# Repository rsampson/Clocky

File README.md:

# Clocky

A simple desk clock for the ESP8266 / ESP32 with a web interface for configuration.

## Features

- Synchronizes time over NTP and automatically corrects for daylight saving time.
- Web interface for setting the time zone, alarm, and Wi-Fi credentials.
- Displays day of week, date, month, and 12-hour time.
- Hourly chime and settable alarm via a piezo beeper. The alarm plays "The Sailor's Hornpipe" on a loop until the touch pad is touched (a short alternative tune can be selected at compile time with `ALARM_TUNE` in [`src/Clocky.cpp`](src/Clocky.cpp)). Alarms have per-day scheduling (e.g. weekdays only) and a "next alarm" readout on the dashboard.
- Three display modes, stepped through with a touch pad: desk clock → stock indexes → sleep → desk clock.
- Stock-index mode that shows the current Dow, S&P 500, and Nasdaq Composite values (fetched from Yahoo Finance every 5 minutes while the mode is selected), each with an up/down marker versus the previous close. If the values can't be fetched (no Wi-Fi, no internet, the data source is down), this mode simply shows the normal clock until they can.
- Sleep mode that suppresses the display light and the hourly chime. The settable alarm still sounds in sleep mode (that's the point of an alarm) and is silenced with a touch.
- OTA (over-the-air) firmware updates via the web interface.

> [!CAUTION]
> This is a hobby project with no guarantees of reliability. Wi-Fi drops, NTP failures, power outages, and plain old bugs can all cause the alarm to not go off. Don't rely on it for anything you can't afford to be late for — the author is not responsible if it fails and you oversleep.

## Hardware Required

- ESP8266 (e.g. ESP12-F) or ESP32 (e.g. Wemos Lolin32)
- SSD1306 OLED display (128x32)
- Piezo beeper (optional — omit if no chime or alarm is needed)
- A touch pad made from any conductive material (required — see below)

### Wiring

| Component        | Pin |
|-------------------|-----|
| Piezo beeper       | D6 and D5 (piezo connected between them, not to GND) |
| Touch pad sensor   | D7  |
| Touch pad driver   | D3 (through a 300k resistor) |
| Status LED         | D4  |

The touch pad is the only input for switching the clock between desk clock, stock-index, and sleep modes, so it is not optional. It works by wiring the conductor directly to input pin D7, and also to output pin D3 through a 300k resistor. Touching the pad adds body capacitance to the circuit, which slows the signal from the driver pin to the sensor pin — this delay is what the firmware detects to register a touch.

The piezo is driven differentially on ESP8266: D5 always carries the inverse of D6, so connecting the piezo between D6 and D5 gives it twice the voltage swing (6.6 V peak to peak instead of 3.3 V), which makes it noticeably louder with no extra parts. A piezo wired from D6 to GND still works, just at the original volume. (ESP32 builds drive D6 only.)

Pin assignments and other hardware constants can be changed in [`src/config.h`](src/config.h).

## Building and Flashing

This is a [PlatformIO](https://platformio.org/) project (see [`platformio.ini`](platformio.ini) for the board configuration and library dependencies).

```bash
pio run                       # build
pio run -t upload             # build and flash over serial
pio device monitor            # serial monitor (115200 baud)
```

## Getting Started

1. Flash the firmware as above.
2. On first boot, the clock starts its own access point. Connect to it and open `192.168.4.1` in a browser.
3. Enter your Wi-Fi router's SSID and password to join the clock to your LAN.
4. Once connected, the clock is reachable at `clocky.local` (mDNS) or the IP assigned by your router.
5. Use the web interface to set the time zone, configure the alarm, and perform OTA firmware updates (no serial connection needed after this point).

### Web Dashboard

| Status | Alarm | Setup |
|---|---|---|
|  |  |  |

## Project Structure

```
platformio.ini    Board configuration and library dependencies
src/
  config.h         Hardware constants: pins, display size, tones, touch sensitivity
  Clocky.cpp        Entry point (setup/loop)
  wifi_manager.*     Wi-Fi connection state machine / AP fallback
  time_manager.*      NTP sync and time zone handling
  web_server.*          AsyncWebServer instance, routes, and JSON REST API
  web_assets.*            Embedded HTML/CSS/JS for the web dashboard
  debug.cpp                  Debug log telemetry
```

## Notes

- Confirm the board setting in [`src/config.h`](src/config.h) matches your actual hardware (ESP32 vs. ESP8266) — a mismatch will cause unpredictable behavior.
- The default hostname is `clocky`; this can be changed in [`src/config.h`](src/config.h).

## License

[MIT](src/LICENSE)

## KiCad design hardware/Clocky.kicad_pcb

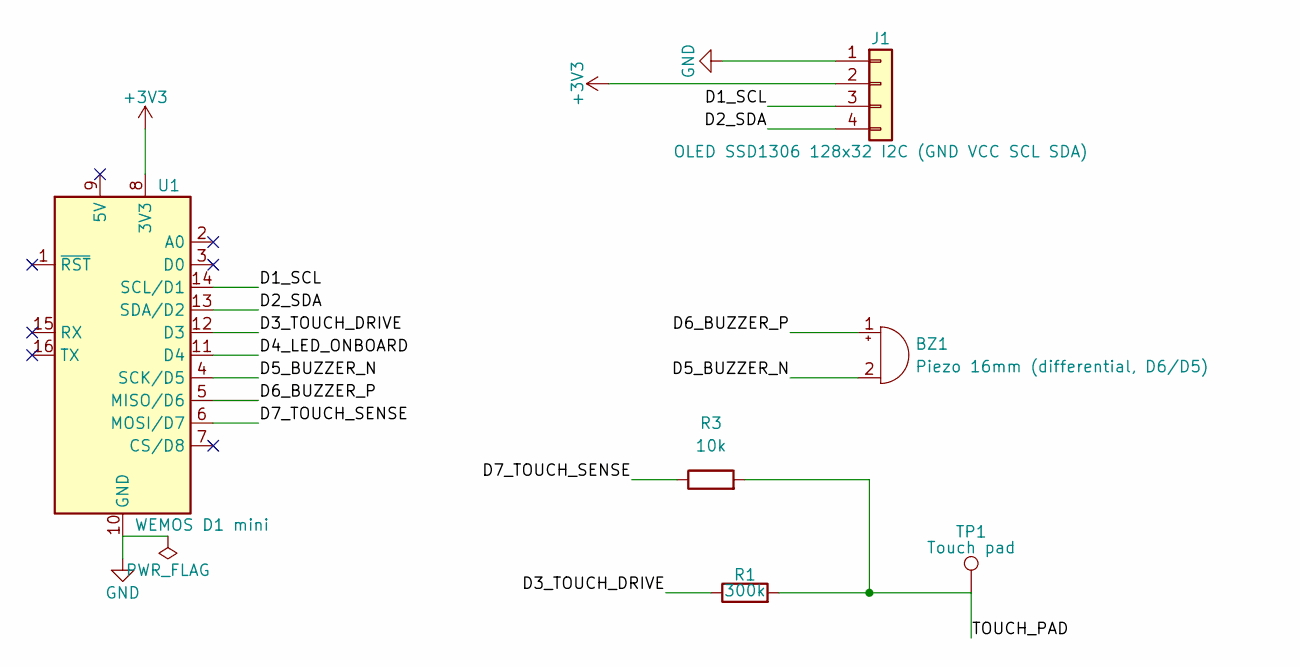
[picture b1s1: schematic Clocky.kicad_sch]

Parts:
BZ1: Piezo 16mm (differential, D6/D5); Buzzer_D16mm_P8mm
J1: OLED SSD1306 128x32 I2C (GND VCC SCL SDA); PinHeader_1x04_P2.54mm_Vertical
R1: 300k; R_Axial_DIN0207_L6.3mm_D2.5mm_P10.16mm_Horizontal
R3: 10k; R_Axial_DIN0207_L6.3mm_D2.5mm_P10.16mm_Horizontal
TP1: Touch pad; TestPoint_Pad_D4.0mm
U1: WEMOS D1 mini; WEMOS_D1_mini_light

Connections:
+3V3: J1.2, U1.8 (3V3)
/D1_SCL: J1.3, U1.14 (SCL/D1)
/D2_SDA: J1.4, U1.13 (SDA/D2)
/D3_TOUCH_DRIVE: R1.1, U1.12 (D3)
/D4_LED_ONBOARD: U1.11 (D4)
/D5_BUZZER_N: BZ1.2 (-), U1.4 (SCK/D5)
/D6_BUZZER_P: BZ1.1 (+), U1.5 (MISO/D6)
/D7_TOUCH_SENSE: R3.1, U1.6 (MOSI/D7)
/TOUCH_PAD: R1.2, R3.2, TP1.1
GND: J1.1, U1.10 (GND)

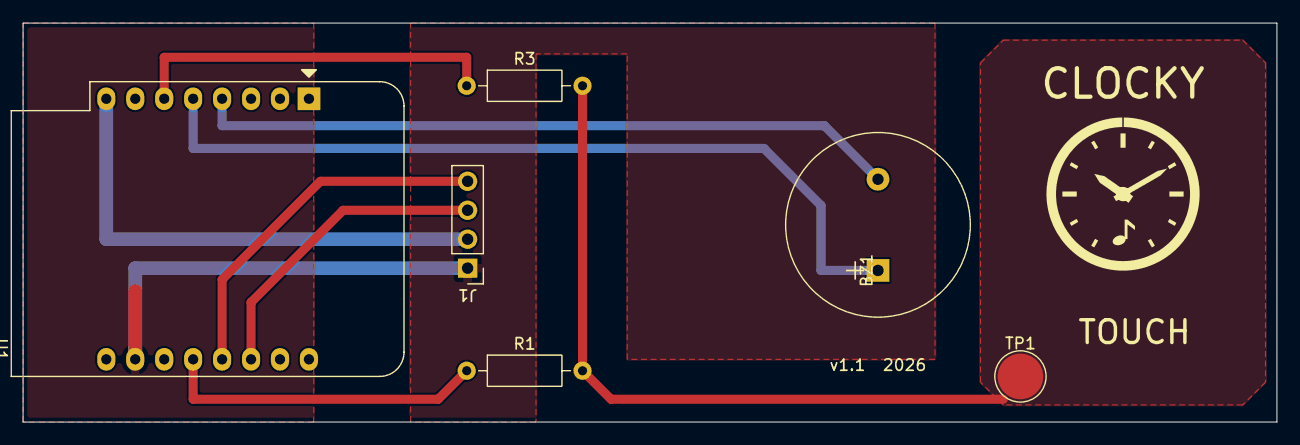
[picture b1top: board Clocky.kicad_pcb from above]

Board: 2 copper layers, 110.0 x 35.0 mm, 6 parts (0 on the bottom side), 9 nets.
